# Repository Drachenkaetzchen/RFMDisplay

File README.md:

Simple RFM display. Birthday present. Ask me for details.

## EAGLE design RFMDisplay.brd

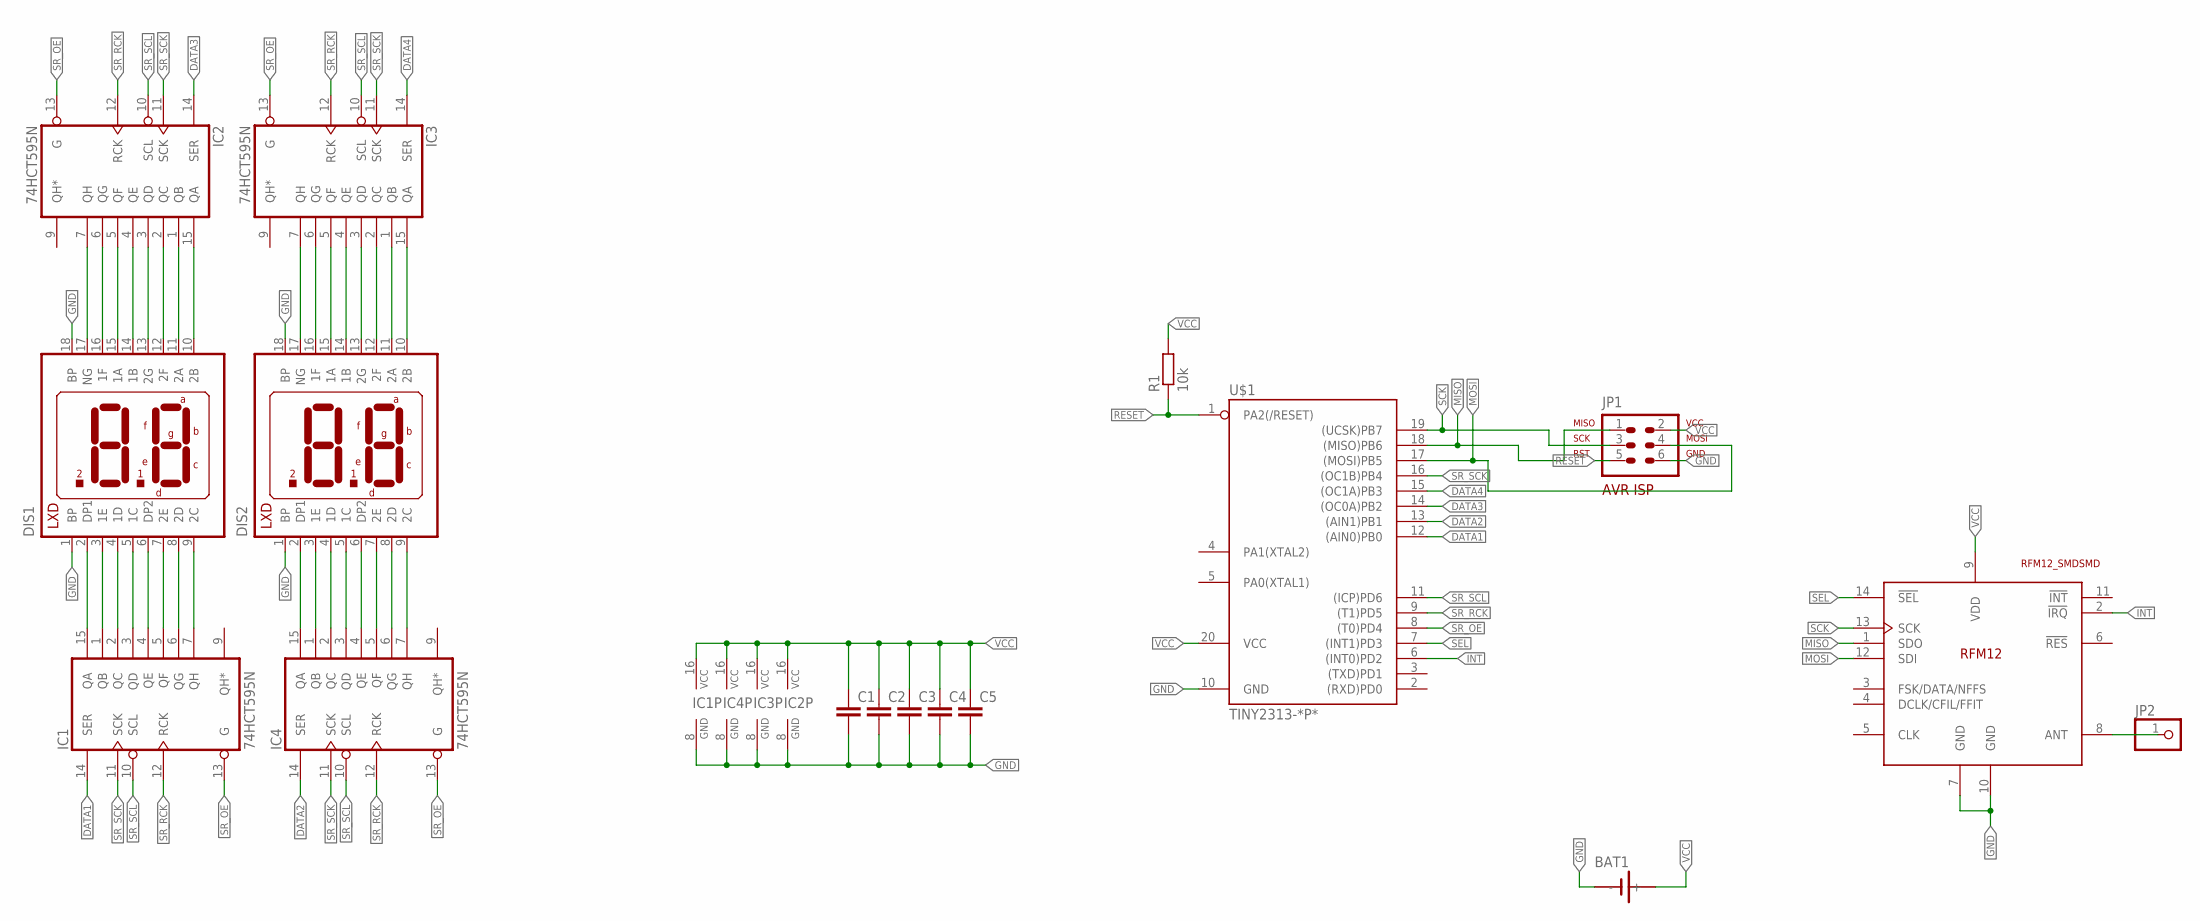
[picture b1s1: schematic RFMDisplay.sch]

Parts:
BAT1: SN2032
C1, C2, C3, C4, C5: C-EUC0805; C0805
DIS1, DIS2: 29DIP; 29-D
IC1, IC2, IC3, IC4: 74HCT595N; DIL16
JP1: AVR-ISP-6VERT; AVR-ISP-6
JP2: PINHD-1X1; 1X01
R1: 10k; R1206
U$1: TINY2313-*P*; DIL20
U$2: RFM12_SMDSMD; RFM12

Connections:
DATA1: IC1.14 (SER), U$1.12 ((AIN0)PB0)
DATA2: IC4.14 (SER), U$1.13 ((AIN1)PB1)
DATA3: IC2.14 (SER), U$1.14 ((OC0A)PB2)
DATA4: IC3.14 (SER), U$1.15 ((OC1A)PB3)
GND: BAT1.-, C1.2, C2.2, C3.2, C4.2, C5.2, DIS1.1 (BP), DIS1.18 (BP), DIS2.1 (BP), DIS2.18 (BP), IC1.8 (GND), IC2.8 (GND), IC3.8 (GND), IC4.8 (GND), JP1.6, U$1.10 (GND), U$2.7 (GND), U$2.10 (GND)
INT: U$1.6 ((INT0)PD2), U$2.2 (!IRQ)
MISO: JP1.1, U$1.18 ((MISO)PB6), U$2.1 (SDO)
MOSI: JP1.4, U$1.17 ((MOSI)PB5), U$2.12 (SDI)
unnamed: DIS1.2 (DP1), IC1.15 (QA)
unnamed: DIS1.3 (1E), IC1.1 (QB)
unnamed: DIS1.4 (1D), IC1.2 (QC)
unnamed: DIS1.5 (1C), IC1.3 (QD)
unnamed: DIS1.6 (DP2), IC1.4 (QE)
unnamed: DIS1.7 (2E), IC1.5 (QF)
unnamed: DIS1.8 (2D), IC1.6 (QG)
unnamed: DIS1.9 (2C), IC1.7 (QH)
unnamed: DIS1.10 (2B), IC2.15 (QA)
unnamed: DIS1.11 (2A), IC2.1 (QB)
unnamed: DIS1.12 (2F), IC2.2 (QC)
unnamed: DIS1.13 (2G), IC2.3 (QD)
unnamed: DIS1.14 (1B), IC2.4 (QE)
unnamed: DIS1.15 (1A), IC2.5 (QF)
unnamed: DIS1.16 (1F), IC2.6 (QG)
unnamed: DIS1.17 (NG), IC2.7 (QH)
unnamed: DIS2.10 (2B), IC3.15 (QA)
unnamed: DIS2.11 (2A), IC3.1 (QB)
unnamed: DIS2.12 (2F), IC3.2 (QC)
unnamed: DIS2.13 (2G), IC3.3 (QD)
unnamed: DIS2.14 (1B), IC3.4 (QE)
unnamed: DIS2.15 (1A), IC3.5 (QF)
unnamed: DIS2.16 (1F), IC3.6 (QG)
unnamed: DIS2.17 (NG), IC3.7 (QH)
unnamed: DIS2.2 (DP1), IC4.15 (QA)
unnamed: DIS2.3 (1E), IC4.1 (QB)
unnamed: DIS2.4 (1D), IC4.2 (QC)
unnamed: DIS2.5 (1C), IC4.3 (QD)
unnamed: DIS2.6 (DP2), IC4.4 (QE)
unnamed: DIS2.7 (2E), IC4.5 (QF)
unnamed: DIS2.8 (2D), IC4.6 (QG)
unnamed: DIS2.9 (2C), IC4.7 (QH)
unnamed: JP2.1, U$2.8 (ANT)
RESET: JP1.5, R1.1, U$1.1 (PA2(/RESET))
SCK: JP1.3, U$1.19 ((UCSK)PB7), U$2.13 (SCK)
SEL: U$1.7 ((INT1)PD3), U$2.14 (!SEL)
SR_OE: IC1.13 (G), IC2.13 (G), IC3.13 (G), IC4.13 (G), U$1.8 ((T0)PD4)
SR_RCK: IC1.12 (RCK), IC2.12 (RCK), IC3.12 (RCK), IC4.12 (RCK), U$1.9 ((T1)PD5)
SR_SCK: IC1.11 (SCK), IC2.11 (SCK), IC3.11 (SCK), IC4.11 (SCK), U$1.16 ((OC1B)PB4)
SR_SCL: IC1.10 (SCL), IC2.10 (SCL), IC3.10 (SCL), IC4.10 (SCL), U$1.11 ((ICP)PD6)
VCC: BAT1.+, C1.1, C2.1, C3.1, C4.1, C5.1, IC1.16 (VCC), IC2.16 (VCC), IC3.16 (VCC), IC4.16 (VCC), JP1.2, R1.2, U$1.20 (VCC), U$2.9 (VDD)

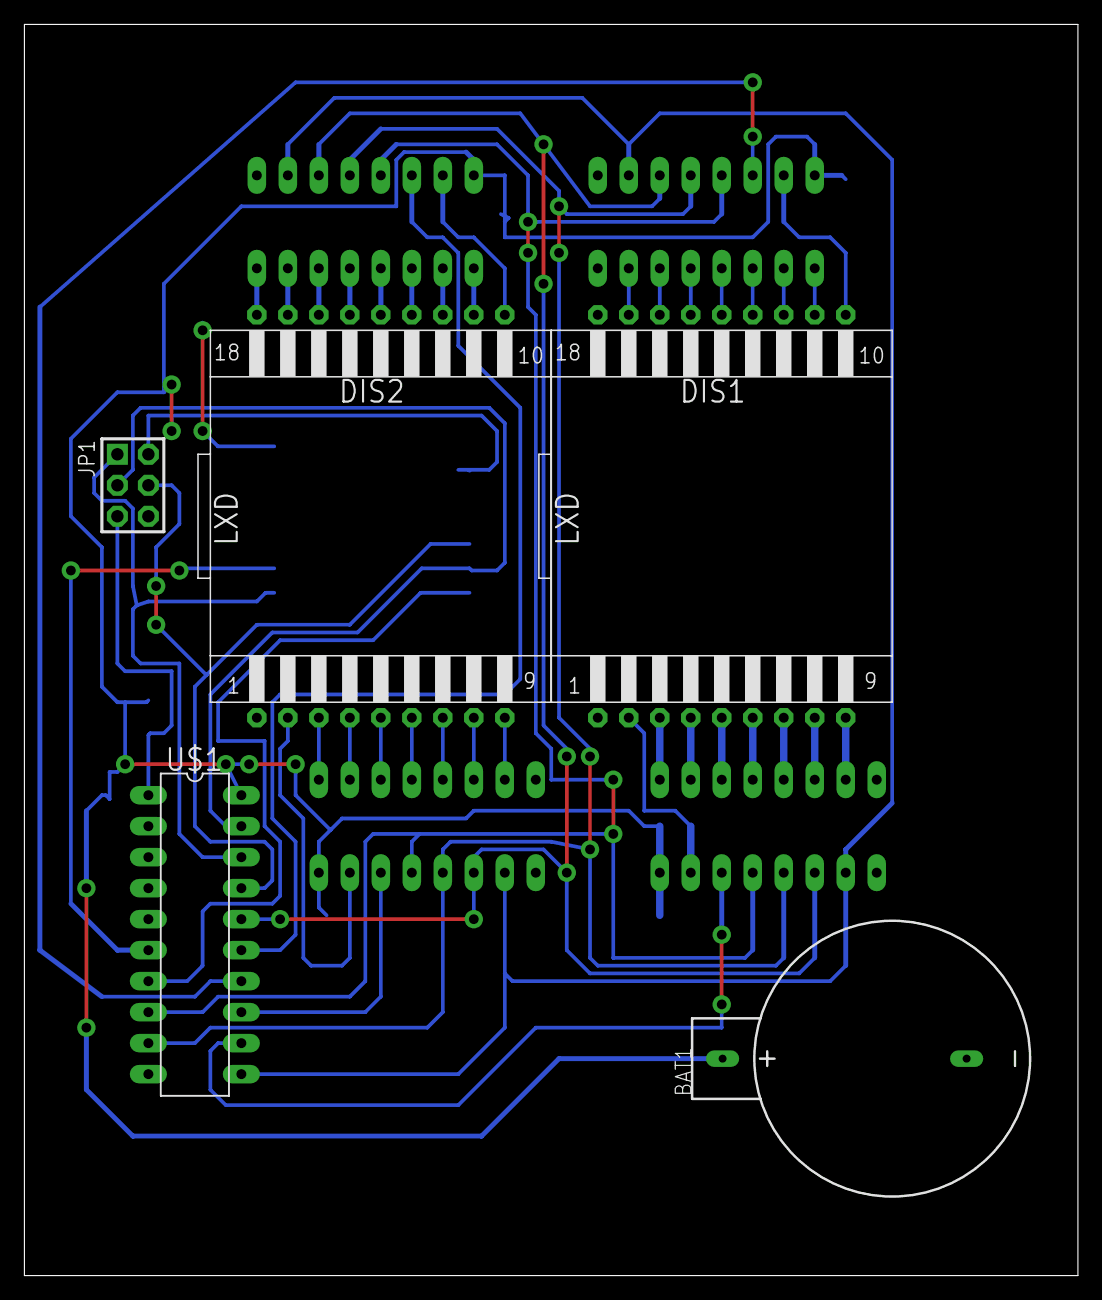
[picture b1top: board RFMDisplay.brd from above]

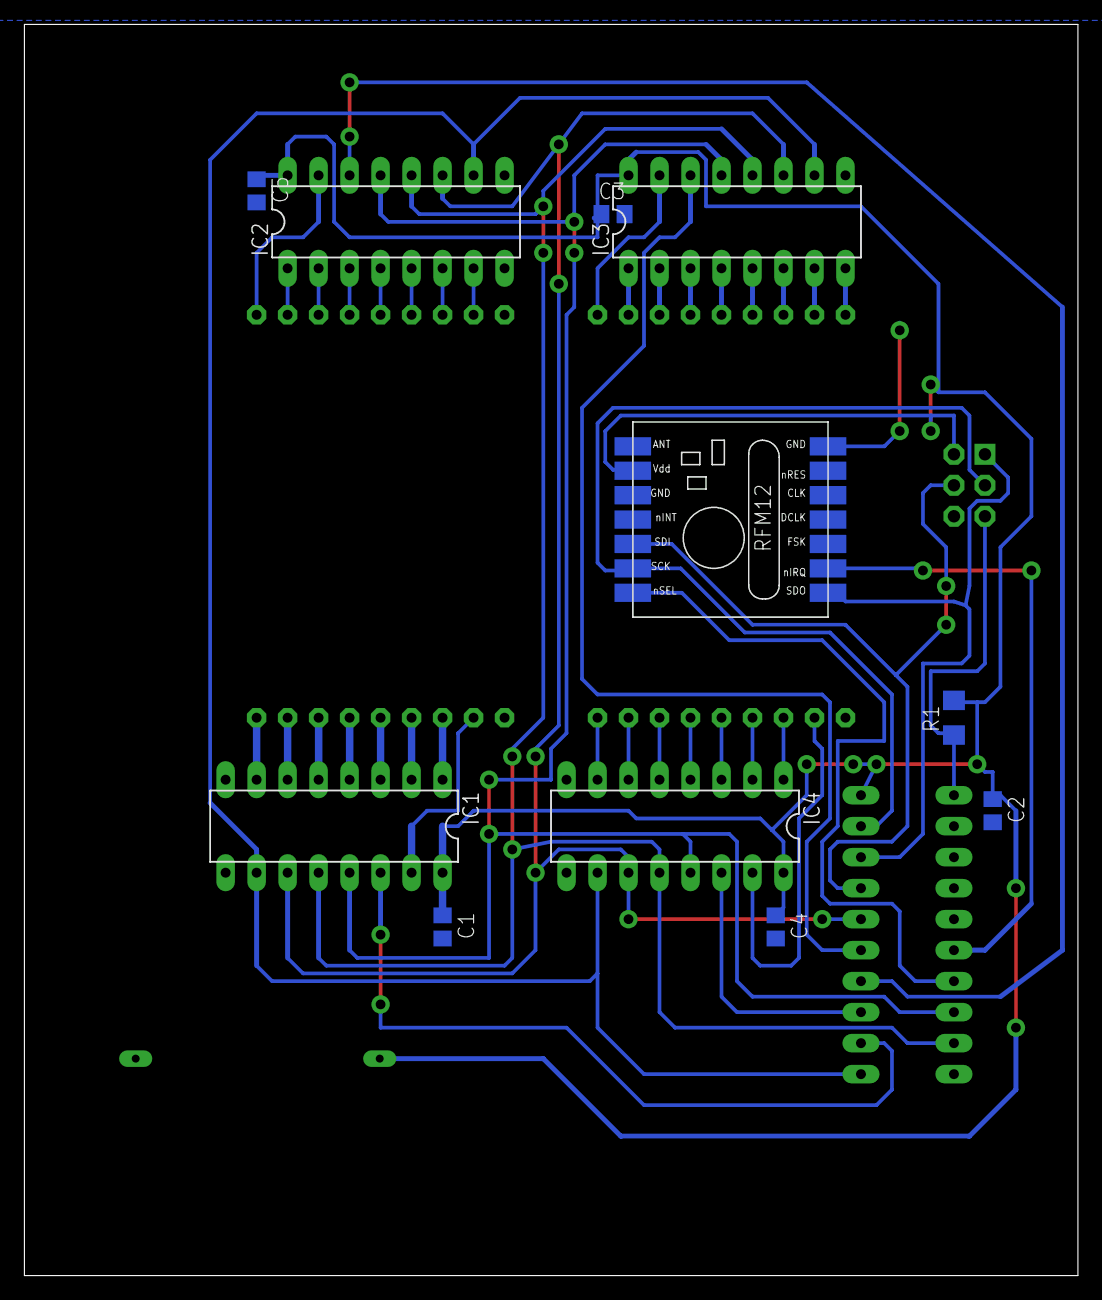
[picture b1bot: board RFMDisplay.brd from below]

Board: 2 copper layers, 86.3 x 102.5 mm, 16 parts (11 on the bottom side), 48 nets.

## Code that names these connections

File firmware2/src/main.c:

#include "rfm12_config.h"
#include <avr/power.h>
#include <avr/interrupt.h>
#include <avr/io.h>
#include <util/delay.h>
#include <avr/wdt.h>
#include <avr/sleep.h>
#include "rfm12lib/rfm12.h"
#define MASK1(b1)                         ( (1<<b1) )
#define MASK2(b1,b2)                      ( (1<<b1) | (1<<b2) )
#define MASK3(b1,b2,b3)                   ( (1<<b1) | (1<<b2) | (1<<b3) )
#define MASK4(b1,b2,b3,b4)                ( (1<<b1) | (1<<b2) | (1<<b3) | (1<<b4) )

#define QUARTER_SECOND_TICKS 20
#define OE PB2
#define MR PD6
#define LATCH PD5
#define CYCLE PD0
#define DATA PB0
#define CLOCK PB4

volatile uint8_t cycle;
volatile uint32_t numberToDisplay;

void main (void) {
	_delay_ms(100);  //little delay for the rfm12 to initialize properly
	rfm12_init();
	setup();
	loop();
}

ISR(TIMER1_COMPA_vect)
{
	refresh();
}

void refresh (void) {
	  uint8_t cnt;

	  if (cycle) {

	    // take the latchPin low so
	    // the LEDs don't change while you're sending in bits:
	    PORTD &= ~(1 << LATCH);

	    for (cnt=0;cnt<32;cnt++) {

	       if (!!(numberToDisplay & (1UL << (31 - cnt)))) {
	         PORTB |= (1 << DATA);
	       } else {
	          PORTB &= ~(1<<DATA);
	       }

	       PORTB |= (1 << CLOCK);
	       PORTB &= ~(1 << CLOCK);


	    }

	    //take the latch pin high so the LEDs will light up:
	    PORTD |= (1 << LATCH);
	    PORTD &= ~(1 << CYCLE);
	  } else {
	     // take the latchPin low so
	    // the LEDs don't change while you're sending in bits:
	    PORTD &= ~(1 << LATCH);

	    for (cnt=0;cnt<32;cnt++) {
	    if (!!(~numberToDisplay & (1UL << (31 - cnt)))) {
	         PORTB |= (1 << DATA);
	       } else {
	        PORTB &= ~(1<<DATA);
	       }
	       PORTB |= (1 << CLOCK);
	       PORTB &= ~(1 << CLOCK);
	    }

	    PORTD |= (1 << LATCH) | (1 << CYCLE);
	  }

	  cycle = !cycle;
}
void setup (void) {
	  DDRD |= (1 << PD5) | (1 << PD6) | (1 << PD0);
	  DDRB |= (1 << PB4) | (1 << PB0);

	  DDRD &= ~(1 << PD2);
	  DDRB &= ~(1 << PB1);

	  PORTB &= ~(1 << OE);
	  PORTD |= (1 << MR);

	  cycle = 0;

	  cli(); // Disable global interrupts


	  // Turn off Input Capture Noise Canceler, Input Capture Edge Select on Falling, stop the clock
	  TCCR1B = (0<<ICNC1) | (0<<ICES1) | (0<<WGM13) | (0<<WGM12) | (0<<CS12) | (0<<CS11) | (0<<CS10);
	  // Disconnect the timer from the output pins, Set Waveform Generation Mode to Normal
	  TCCR1A = (0<<COM1A1) | (0<<COM1A0) | (0<<COM1B1) | (0<<COM1B0) | (0<<WGM11) | (0<<WGM10);
	  // Reset the count to zero
	  TCNT1 = 0;
	  // Set the output compare registers to zero
	  OCR1A = 0;
	  OCR1B = 0;
	  // Clear the input capture?
	  // ICR1 = 0;
	  // Disable all Timer1 interrupts
	  TIMSK &= ~(1 << TOIE1 | 1 << OCIE1A | 1 << OCIE1B | 1 << ICIE1);
	  // Clear the Timer1 interrupt flags
	  TIFR |= MASK4(TOV1,OCF1A,OCF1B,ICF1);

	  OCR1A = QUARTER_SECOND_TICKS;

	  TCCR1A = (TCCR1A & ~MASK2(WGM11,WGM10)) | (((4 & 3) >> 0) << WGM10);
	  TCCR1B = (TCCR1B & ~MASK2(WGM13,WGM12)) | (((4 & 12) >> 2) << WGM12);
	  TCCR1B = (TCCR1B & ~MASK3(CS12,CS11,CS10)) | (4 << CS10);
	  TIMSK |= (1<<OCIE1A);
	  sei(); // Enable global interrupts

	  numberToDisplay = 0;
}

void loop() {
	uint8_t delay=0;
	numberToDisplay=0;
	while (1) {
	delay++;

	if (delay > 254) {
		delay = 0;
		numberToDisplay++;
		/*if (numberToDisplay == 1UL) {
			numberToDisplay = 0UL;
		} else {
			numberToDisplay = 1UL;
		}*/
	}

	if (rfm12_rx_status() == STATUS_COMPLETE)
  	{
		rfm12_rx_clear();
		numberToDisplay = 4294967295UL;
		_delay_ms(100);
		numberToDisplay = 127;
  	}

	rfm12_tick();

	}
}

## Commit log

2013-11-06 Increased pad size
2013-11-07 Adjusted some wire widths
2013-11-07 Initial shift register test
2013-11-08 Added stuff…not exactly a good commit msg
2013-11-10 More fooy
2013-11-15 Added more stuff
2013-11-27 Removed old firmware stuff
2013-11-27 Added gitignore
2013-11-27 More or less clean source checkin
2013-11-27 Some adjustments for low power stuff, added buffer implementation
2013-11-28 Fixed sleep interval to be really 10 minutes
